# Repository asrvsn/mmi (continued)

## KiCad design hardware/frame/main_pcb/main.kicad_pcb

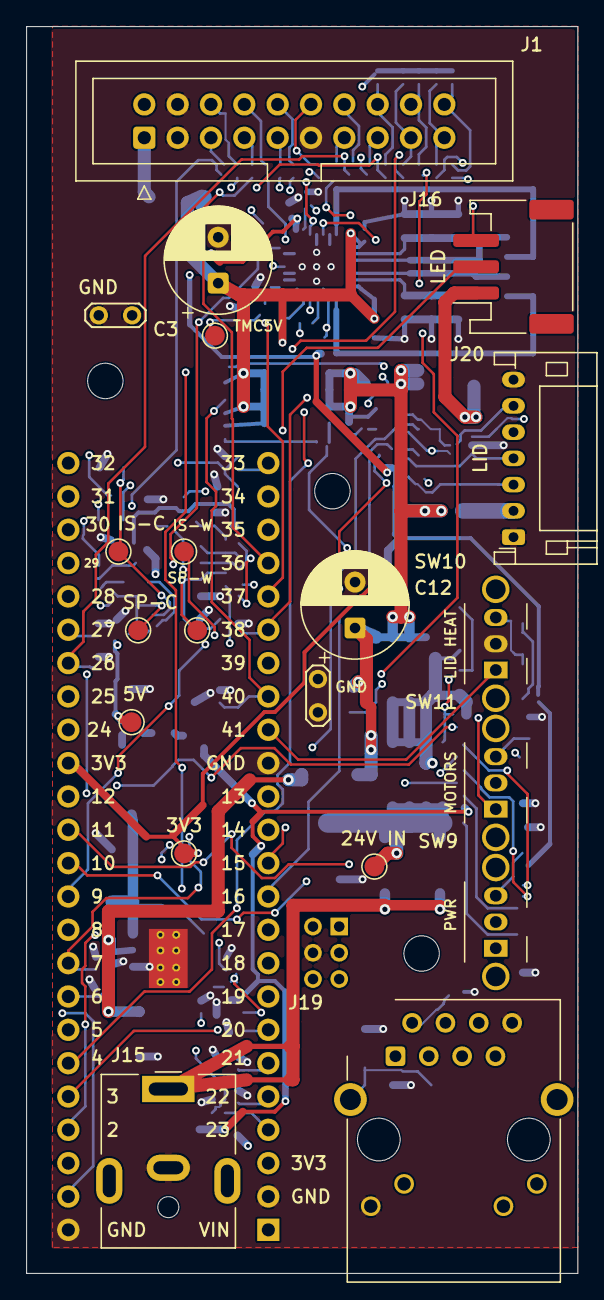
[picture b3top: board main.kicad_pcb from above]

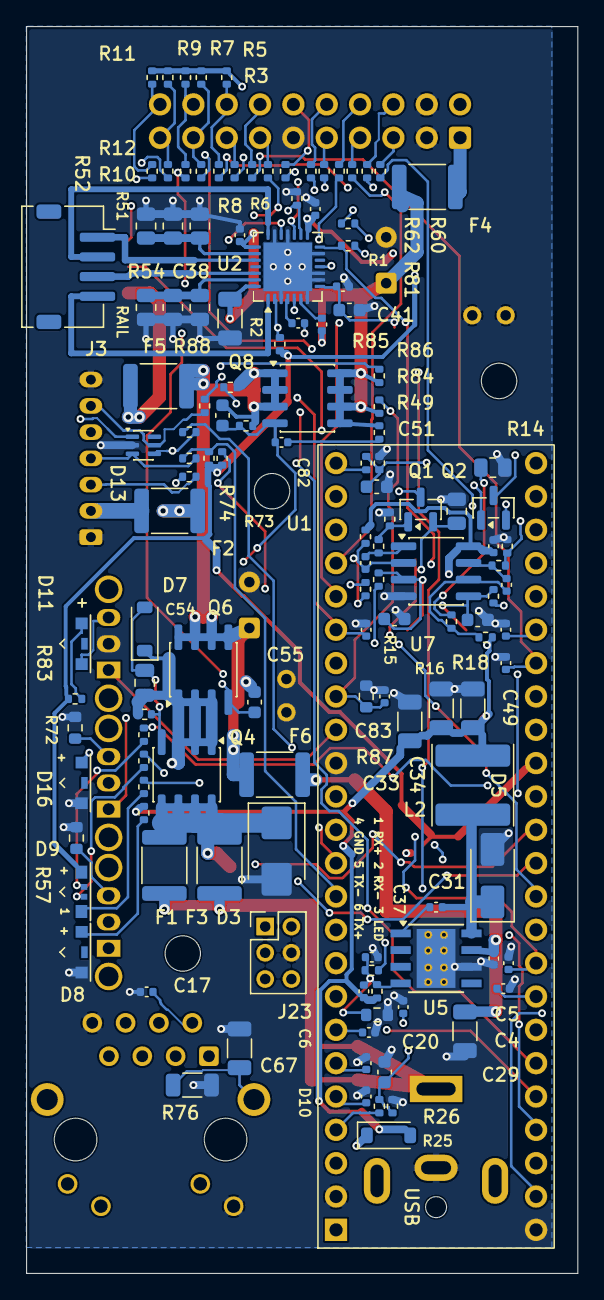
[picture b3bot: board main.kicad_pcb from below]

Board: 4 copper layers, 42.0 x 95.0 mm, 158 parts (135 on the bottom side), 113 nets.

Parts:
C2, C17, C30, C36, C39, C82: 100n 50V; C_0402_1005Metric
C3, C12: 100u 50V; CP_Radial_D8.0mm_P3.50mm
C4, C5, C6, C7, C8, C13, C14, C15, C42, C43, C83: 100n; C_0402_1005Metric
C20, C50, C51, C52: 470n 25V; C_0603_1608Metric
C29, C38: 10u 50V; C_1206_3216Metric
C31, C47, C48, C49: 10n 50V; C_0402_1005Metric
C32, C33, C34: 22u 25V; C_1206_3216Metric
C35: 1n 50V; C_0402_1005Metric
C37: 100p 50V; C_0402_1005Metric
C40: 22n 50V; C_0402_1005Metric
C41: 4u7 16V; C_0603_1608Metric
C54: 2u2 50V; C_0805_2012Metric
C55: 47n 50V; C_0603_1608Metric
C67: 1n 2kV; C_1206_3216Metric
C81: 1u 50V; C_0603_1608Metric
D3: SMBJ24CA; D_SMB
D5: SS34; D_SMA
D7: BZT52C12; D_SOD-123
D8: XL-3210UGC; LED_SideView_XL-3210
D9: XL-3210RGBC-YG; LED_RGB_SideView_XL-3210RGBC
D10: B5819W; D_SOD-123
D11: XL-3210SURC; LED_SideView_XL-3210
D13: SMF05CT1G; SOT-363_SC-70-6
D16: XL-3210UYC; LED_SideView_XL-3210
F1, F2, F3, F4: PTC 1.1 A 33 V; Fuse_1812_4532Metric
F5, F6: PTC 0.5 A 30 V; Fuse_1812_4532Metric
J1: Ribbon header 2x10 (vertical, shrouded); IDC-Header_2x10_P2.54mm_Vertical
J3: Rail motor (ZH); JST_ZH_S4B-ZR-SM4A-TF_1x04-1MP_P1.50mm_Horizontal
J15: 24 V in; BarrelJack_CUI_PJ-063AH_Horizontal
J16: LED strip (JST PH); JST_PH_S3B-PH-SM4-TB_1x03-1MP_P2.00mm_Horizontal
J19: RJ45 MagJack (J1B1211CCD); RJ45_Cetus_J1B1211CCD_Horizontal
J20: Lid port (JST PH, 7); JST_PH_S7B-PH-K_1x07_P2.00mm_Horizontal
J23: ETH (kit cable); PinHeader_2x03_P2.00mm_Vertical
L2: 22u 2.05A; L_Sunlord_SWPA6045S
MH1, MH2, MH3: M2.5; MountingHole_2.7mm_M2.5
Q1, Q2: HL2310A; SOT-23
Q4, Q6, Q8: AO4485; SOIC-8_3.9x4.9mm_P1.27mm
R1, R4, R6, R8, R10, R12, R15, R16, R19, R20, R60, R61, R62, R63, R64, R65, R67, R72, R77, R84, R88: 1k; R_0402_1005Metric
R2, R25, R28, R45, R46, R47, R48, R50: 10k; R_0402_1005Metric
R3, R5, R7, R9, R11: 2k; R_0402_1005Metric
R13, R14: 49.9; R_0805_2012Metric
R17, R18, R56: 1M; R_0402_1005Metric
R21, R22, R55, R82, R86: 100k; R_0402_1005Metric
R26, R49: 15k; R_0402_1005Metric
R29, R30, R31, R32: 100; R_0402_1005Metric
R37: 12k; R_0402_1005Metric
R38: 3k9; R_0603_1608Metric
R39, R68, R69: 470; R_0402_1005Metric
R40, R41, R51, R52, R53, R54: 1R 0805; R_0805_2012Metric
R57: 470k; R_0603_1608Metric
R66, R73, R74: 2k2; R_0402_1005Metric
R76: 1M; R_1206_3216Metric
R81, R85: 22k; R_0402_1005Metric
R83: 150k; R_0603_1608Metric
R87: 13k; R_0603_1608Metric
SW9, SW10, SW11: C&K SK-12D07-VG 4 NS PA; SW_Slide_SPDT_Angled_SK-12D07_H8
TP1: 24V IN; TestPoint_Pad_D1.5mm
TP2: 5V; TestPoint_Pad_D1.5mm
TP3: 3V3; TestPoint_Pad_D1.5mm
TP4, TP5: GND; TestPoint_2Pads_Pitch2.54mm_Drill0.8mm
TP6: TMC5V; TestPoint_Pad_D1.5mm
TP7: SP-W; TestPoint_Pad_D1.5mm
TP8: SP-C; TestPoint_Pad_D1.5mm
TP9: IS-W; TestPoint_Pad_D1.5mm
TP10: IS-C; TestPoint_Pad_D1.5mm
U1: Teensy 4.1; Teensy41_Ethernet
U2: TMC2209-LA; VQFN-28-1EP_5x5mm_P0.5mm_EP3.7x3.7mm
U5: TPS5430DDA; TI_SO-PowerPAD-8_ThermalVias
U7: MCP6002T-I/SN; SOIC-8_3.9x4.9mm_P1.27mm

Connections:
+3V3: C43.1, D9.2, R2.1, R3.1, R5.1, R7.1, R9.1, R11.1, R72.1, R73.1, R74.1, TP3.1, U1.3V3, U2.15
+5V: C13.1, C32.1, C33.1, C34.1, C35.1, D10.2, L2.2, R17.2, R18.2, R37.1, R66.1, TP2.1, U7.8
+24V: C12.1, C55.2, C81.2, F2.1, F5.1, F6.1, Q6.5, Q6.6, Q6.7, Q6.8, Q8.1, Q8.2, Q8.3, R82.2, R88.2
/DAC_C: C52.1, R50.2, TP8.1, U7.5
/DAC_W: C50.1, R28.2, TP7.1, U7.3
/DIAG: U1.5, U2.11
/DIM_C: R48.1, U1.33
/DIM_W: R25.1, U1.23
/DIR: U1.3, U2.19
/EN: R2.2, U1.4, U2.2
/ETH_CT: C17.1, J19.2, J19.5
/ETH_LED: J19.10, J23.3
/ETH_RX+: J19.4, J23.1
/ETH_RX-: J19.6, J23.2
/ETH_TX+: J19.1, J23.6
/ETH_TX-: J19.3, J23.5
/FB5: C35.2, C37.1, R37.2, R38.1, R39.1, U5.4
/HEAD_24V: F4.2, J1.1, J1.2
/ISNS_C: Q2.2, R14.1, R16.2, TP10.1
/ISNS_W: Q1.2, R13.1, R15.2, TP9.1
/LED_24V: F5.2, J16.1
/LED_B: R69.2, U1.12
/LED_C-: J16.3, Q2.3
/LED_G: R68.2, U1.11
/LED_R: R67.2, U1.10
/LED_W-: J16.2, Q1.3
/LID_24V: F2.2, J20.2
/LID_IN1: R31.1, U1.14
/LID_IN1_P: D13.4, J20.5, R31.2
/LID_IN2: R32.1, U1.15
/LID_IN2_P: D13.5, J20.6, R32.2
/LID_SW: SW10.1, U1.41
/LIM_MAX: C5.1, R6.1, U1.7
/LIM_MIN: C4.1, R4.1, U1.6
/LIM_X: C6.1, R8.1, U1.20
/LIM_Y: C7.1, R10.1, U1.21
/LIM_Z: C8.1, R12.1, U1.22
/MOT_24V: C2.1, C3.1, C38.1, C39.1, F4.1, Q8.5, Q8.6, Q8.7, Q8.8, R84.1, R85.1, R86.1, U2.22, U2.28
/MOT_G: C81.1, C82.2, Q8.4, R82.1, SW11.2
/MOT_LED: D16.2, R85.2
/MOT_M: C82.1, R84.2
/MOT_ON: C83.1, R86.2, R87.1, U1.40
/MX_I: C47.1, R45.2, U1.27
/MX_IN1: R60.1, U1.28
/MX_IN1_C: J1.5, R60.2
/MX_IN2: R61.1, U1.29
/MX_IN2_C: J1.6, R61.2
/MX_IP: J1.12, R45.1
/MY_I: C48.1, R46.2, U1.38
/MY_IN1: R62.1, U1.36
/MY_IN1_C: J1.7, R62.2
/MY_IN2: R63.1, U1.37
/MY_IN2_C: J1.8, R63.2
/MY_IP: J1.13, R46.1
/MZ_I: C49.1, R47.2, U1.26
/MZ_IN1: R64.1, U1.24
/MZ_IN1_C: J1.9, R64.2
/MZ_IN2: R65.1, U1.25
/MZ_IN2_C: J1.10, R65.2
/MZ_IP: J1.14, R47.1
/PH_5V: C31.1, D5.1, L2.1, U5.8
/PWR_G: C54.2, C55.1, D7.2, Q4.4, Q6.4, R56.2, SW9.2
/PWR_IN: D3.1, F1.2, F3.2, Q4.5, Q4.6, Q4.7, Q4.8, TP1.1
/PWR_S: C54.1, D7.1, Q4.1, Q4.2, Q4.3, Q6.1, Q6.2, Q6.3, R56.1, SW9.1
/RAIL_A1: J3.1, U2.24
/RAIL_A2: J3.2, U2.21
/RAIL_B1: J3.3, U2.26
/RAIL_B2: J3.4, U2.1
/SCL1: R30.1, R74.2, U1.16
/SCL1_P: D13.3, J20.4, R30.2
/SDA1: R29.1, R73.2, U1.17
/SDA1_P: D13.1, J20.3, R29.2
/SENSE_A: R40.1, R51.1, R52.1, U2.23
/SENSE_B: R41.1, R53.1, R54.1, U2.27
/STEP: R55.1, U1.2, U2.16
/SW10_ON: D11.1, SW10.3
/SW11_OFF: R88.1, SW11.1
/SW11_ON: R83.1, SW11.3
/SW_MAX: J1.17, R5.2, R6.2
/SW_MIN: J1.16, R3.2, R4.2
/SW_X: J1.18, R7.2, R8.2
/SW_Y: J1.19, R9.2, R10.2
/SW_Z: J1.20, R11.2, R12.2
/TMC_5V: C41.1, C42.1, R81.2, TP6.1, U2.8
/UART_RX: R1.2, U1.0, U2.14
/UART_TX: R1.1, U1.1
/V9_OFF: R77.1, U1.9
/V9_OFF_C: J1.15, R77.2
/VIN5: C29.1, C30.1, F6.2, U5.7
/VIN_JACK: F1.1, F3.1, J15.1
/VIN_T: D10.1, U1.VIN
GND: C2.2, C3.2, C4.2, C5.2, C6.2, C7.2, C8.2, C12.2, C13.2, C17.2, C20.2, C29.2, C30.2, C32.2, C33.2, C34.2, C36.2, C37.2, C38.2, C41.2, C42.2, C43.2, C47.2, C48.2, C49.2, C50.2, C51.2, C52.2, C67.2, C83.2, D3.2, D5.2, D8.1, D13.2, D16.1, J1.3, J1.4, J1.11, J15.2, J19.8, J19.9, J20.1, J20.7, J23.4, R13.2, R14.2, R21.2, R22.2, R26.2, R38.2, R40.2, R41.2, R49.2, R51.2, R52.2, R53.2, R54.2, R55.2, R57.2, R76.2, R83.2, R87.2, SW10.2, TP4.1, TP4.2, TP5.1, TP5.2, U1.GND, U2.3, U2.7, U2.9, U2.10, U2.13, U2.18, U2.20, U2.29, U5.6, U5.9, U7.4
unnamed: C14.2, R19.1, U7.1
unnamed: C15.2, R20.1, U7.7
unnamed: C20.1, R25.2, R26.1, R28.1
unnamed: C36.1, R39.2
unnamed: C51.1, R48.2, R49.1, R50.1
unnamed: D8.2, R66.2
unnamed: D9.4, R69.1
unnamed: D9.3, R68.1
unnamed: D9.1, R67.1
unnamed: D11.2, R72.2
unnamed: C67.1, J19.13, R76.1
unnamed: Q1.1, R19.2, R21.1
unnamed: Q2.1, R20.2, R22.1
unnamed: R57.1, SW9.3
unnamed: C40.2, U2.5
unnamed: C40.1, U2.4
unnamed: C39.2, U2.6
unnamed: R81.1, U2.17
unnamed: C31.2, U5.1
unnamed: C14.1, R15.1, R17.1, U7.2
unnamed: C15.1, R16.1, R18.1, U7.6

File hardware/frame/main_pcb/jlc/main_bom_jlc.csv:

Comment,Designator,Footprint,LCSC Part #
100n 50V,"C2,C17,C30,C36,C39,C82",C_0402_1005Metric,C307331
100n,"C4,C5,C6,C7,C8,C13,C14,C15,C42,C43,C83",C_0402_1005Metric,C1525
470n 25V,"C20,C50,C51,C52",C_0603_1608Metric,C1623
10u 50V,"C29,C38",C_1206_3216Metric,C13585
10n 50V,"C31,C47,C48,C49",C_0402_1005Metric,C15195
22u 25V,"C32,C33,C34",C_1206_3216Metric,C12891
1n 50V,C35,C_0402_1005Metric,C1523
100p 50V,C37,C_0402_1005Metric,C1546
22n 50V,C40,C_0402_1005Metric,C1532
4u7 16V,C41,C_0603_1608Metric,C19666
2u2 50V,C54,C_0805_2012Metric,C377773
47n 50V,C55,C_0603_1608Metric,C1622
1n 2kV,C67,C_1206_3216Metric,C9196
1u 50V,C81,C_0603_1608Metric,C15849
SMBJ24CA,D3,D_SMB,C19077579
SS34,D5,D_SMA,C8678
BZT52C12,D7,D_SOD-123,C19077410
XL-3210UGC,D8,LED_SideView_XL-3210,C965877
XL-3210RGBC-YG,D9,LED_RGB_SideView_XL-3210RGBC,C965884
B5819W,D10,D_SOD-123,C8598
XL-3210SURC,D11,LED_SideView_XL-3210,C965874
SMF05CT1G,D13,SOT-363_SC-70-6,C15879
XL-3210UYC,D16,LED_SideView_XL-3210,C965876
PTC 1.1 A 33 V,"F1,F2,F3,F4",Fuse_1812_4532Metric,C142747
PTC 0.5 A 30 V,"F5,F6",Fuse_1812_4532Metric,C151168
22u 2.05A,L2,L_Sunlord_SWPA6045S,C83454
HL2310A,"Q1,Q2",SOT-23,C7420347
AO4485,"Q4,Q6,Q8",SOIC-8_3.9x4.9mm_P1.27mm,C51499
1k,"R1,R4,R6,R8,R10,R12,R15,R16,R19,R20,R60,R61,R62,R63,R64,R65,R67,R72,R77,R84,R88",R_0402_1005Metric,C11702
10k,"R2,R25,R28,R45,R46,R47,R48,R50",R_0402_1005Metric,C25744
2k,"R3,R5,R7,R9,R11",R_0402_1005Metric,C4109
49.9,"R13,R14",R_0805_2012Metric,C17720
1M,"R17,R18,R56",R_0402_1005Metric,C26083
100k,"R21,R22,R55,R82,R86",R_0402_1005Metric,C25741
15k,"R26,R49",R_0402_1005Metric,C25756
100,"R29,R30,R31,R32",R_0402_1005Metric,C25076
12k,R37,R_0402_1005Metric,C25752
3k9,R38,R_0603_1608Metric,C23018
470,"R39,R68,R69",R_0402_1005Metric,C25117
1R 0805,"R40,R41,R51,R52,R53,R54",R_0805_2012Metric,C25271
470k,R57,R_0603_1608Metric,C23178
2k2,"R66,R73,R74",R_0402_1005Metric,C25879
1M,R76,R_1206_3216Metric,C17927
22k,"R81,R85",R_0402_1005Metric,C25768
150k,R83,R_0603_1608Metric,C22807
13k,R87,R_0603_1608Metric,C22797
TMC2209-LA,U2,VQFN-28-1EP_5x5mm_P0.5mm_EP3.7x3.7mm,C2150710
TPS5430DDA,U5,TI_SO-PowerPAD-8_ThermalVias,C9864
MCP6002T-I/SN,U7,SOIC-8_3.9x4.9mm_P1.27mm,C7377

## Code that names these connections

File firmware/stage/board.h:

// Pins and fixed hardware facts: ../hardware.md "Pins and timers", checked against the main and head netlists
// (2026-10-18). Values here are hardware, not settings: parameters.yaml can't move them.
#pragma once
#include <stdint.h>

namespace pin {
constexpr uint8_t TMC_RX = 0, TMC_TX = 1;   // Serial1; TX through R1 1k to PDN_UART, RX on it: we hear our own echo
constexpr uint8_t STEP = 2, DIR = 3;
constexpr uint8_t EN = 4;                   // TMC2209 enable, low = on (R2 pulls it high). Never analogWrite (pin 33)
constexpr uint8_t DIAG = 5;
constexpr uint8_t LIM_MIN = 6, LIM_MAX = 7; // rail switches; never analogWrite 7 (pin 25)
constexpr uint8_t V9_OFF = 9;               // high = the head's 9 V buck off
constexpr uint8_t LED_R = 10, LED_G = 11, LED_B = 12;   // D9, low = on
constexpr uint8_t LID_IN1 = 14, LID_IN2 = 15;           // the lid's DRV8871 (lid.cpp): coast PWM, or both low
constexpr uint8_t LIM_X = 20, LIM_Y = 21, LIM_Z = 22;   // each fine axis's hi + lo switches in series
constexpr uint8_t DIM_W = 23, DIM_C = 33;               // LED strip set-points (light.cpp): 12-bit PWM, low = dark
constexpr uint8_t MOT_ON = 40;              // SW11: high = the motors' 24 V is up
constexpr uint8_t LID_SW = 41;              // SW10: low = lid heater off
// Fine axes in order x, y, z: DRV8251A IN1 / IN2 (PWM between drive and brake) and IPROPI.
constexpr uint8_t IN1[3] = {28, 36, 24};
constexpr uint8_t IN2[3] = {29, 37, 25};
constexpr uint8_t IPROPI[3] = {27, 38, 26}; // A13, A14, A12
constexpr uint8_t LIM_FINE[3] = {LIM_X, LIM_Y, LIM_Z};
constexpr uint8_t FREE[] = {8, 13, 18, 19, 30, 31, 32, 34, 35, 39};
}  // namespace pin

namespace hw {
constexpr float VM = 9.16f;                 // the head's motor rail, V
constexpr float IPROPI_V_PER_A = 3.15f;     // 1575 uA/A into 2k0 on the head
constexpr float ADC_FULL_V = 3.3f;          // 12-bit ADC against the Teensy's 3.3 V
constexpr float DUTY_CEIL = 0.92f;          // MUST: fine motors average <= ~8.4 V
constexpr float FINE_V_CEIL = 400.0f;       // um/s: no setting may ask more of a fine axis
constexpr float RAIL_V_CEIL = 20000.0f;     // um/s
constexpr uint8_t RAIL_IRUN_CEIL = 28;      // (28+1)/32 x 0.657 A = 0.60 A rms, the NEMA11's rating
constexpr uint32_t WAKE_US = 300;           // DRV8251A t_WAKE 250 us: brake this long before the first PWM
constexpr uint32_t REST_BRAKE_MS = 100;     // at rest: brake, then coast (the drivers sleep)
constexpr uint32_t STALL_MS_CEIL = 80;      // MUST: a stall stops within 0.1 s
constexpr uint32_t MOT_DEBOUNCE_MS = 50;    // MOT_ON steady high before acting on it
constexpr uint32_t HEAD_9V_MS = 100;        // the head's soft start + buck after MOT_24V
constexpr uint32_t LIMIT_CONFIRM_US = 3000; // a limit input must stay high this long to count (it stops at once anyway)
constexpr uint32_t LIGHT_PWM_HZ = 36621;    // the LED set-points: 150 MHz / 4096, so 12 bits are one count each
// The lid (../hardware.md "Lid"; the ADCs' inputs checked against lid v16's netlist, ../../hardware/lid/heating_pcb,
// 2026-10-30).
constexpr uint32_t LID_PWM_HZ = 20000;      // the bridge's coast PWM: inaudible, and the DRV8871's 800 ns pulse is 1.6 %
constexpr float LID_DUTY_CEIL = 80.0f;      // %: lid.duty_max can't pass it (the 9.16 V supply's full drive is 6.1 W)
constexpr float LID_DUTY_FLOOR = 2.0f;      // %: under it, 0 (a pulse too short to be sure to register)
constexpr uint32_t LID_WAKE_US = 60;        // MUST: the active input high this long before the PWM (wake 5 us + t_ON 50)
constexpr uint32_t LID_SW_MS = 20;          // SW10 steady on this long before driving again
constexpr float LID_BOARD_MAX_C = 60.0f;    // MUST: a board NTC at this cuts the drive (../hardware.md "Lid")
constexpr float LID_MEDIUM_CEIL = 50.0f;    // C: lid.medium_max can't pass it
// The NTCs' two rates: each sampled every 62.5 ms (16 Hz), and a readout of the last
// 16, their mean and SD, once a second (1 Hz): the thermal loop's period and !lid's. 16 samples a second fall evenly
// over a cycle of 50 and of 60 Hz mains, so pickup from either averages out of the mean (10, 20 or 25 Hz don't).
constexpr uint32_t LID_POLL_US = 62500;
constexpr uint8_t LID_WINDOW = 16;
constexpr uint32_t ADS_CONV_US = 9000;      // an ADS1115 conversion at 128 SPS: 7.8 ms, +10 % for its clock
constexpr uint32_t ADS_LATE_US = 30000;     // ... and one that hasn't finished by this is a fault (the lid's gone)
constexpr uint8_t ADS_U4 = 0x48, ADS_U3 = 0x49;   // ADDR to GND / to VDD
constexpr float ADS_FS_V = 4.096f;          // the NTC channels' PGA: 12.3 C and below would saturate at 2.048 V
constexpr float NTC_B_BOARD = 3380.0f;      // RT1-RT3, Murata NCP18XH103F03RB: B25/50 (its "3435" is B25/85)
constexpr float NTC_B_PROBE = 3977.0f;      // J2, J3: TEWA TT4-G10KC3 medium probes, 10k 1 %
constexpr float LID_V33 = 3.3f, LID_V33_TOL = 0.05f;   // the lid's 3.3 V: within 5 %, or no NTC reading is trusted
}  // namespace hw

// The TMC2209 (rail). Its fixed configuration, hardware.md "Rail": everything but IRUN lives here.
namespace tmc {
constexpr uint32_t BAUD = 115200;
constexpr uint8_t ADDR = 0;                 // MS1 = MS2 = GND
constexpr uint8_t VERSION = 0x21;           // IOIN[31:24]
constexpr float RSENSE = 0.33f;             // 3 x 1R per coil
// GCONF: pdn_disable, mstep_reg_select, multistep_filt. MUST: never internal_Rsense (bit 1); never OTP_PROG.
constexpr uint32_t GCONF = (1u << 6) | (1u << 7) | (1u << 8);
constexpr uint8_t TOFF = 4, HSTRT = 5, HEND = 0, TBL = 1;
constexpr uint8_t IHOLD = 0, IHOLDDELAY = 2, TPOWERDOWN = 5;   // ramp to zero current at standstill, then EN high
constexpr uint32_t PWMCONF = 0xC10D0E24;    // reset value with PWM_GRAD 14: autoscale + autograd on
constexpr float CLK_HZ = 12e6f;
}  // namespace tmc
